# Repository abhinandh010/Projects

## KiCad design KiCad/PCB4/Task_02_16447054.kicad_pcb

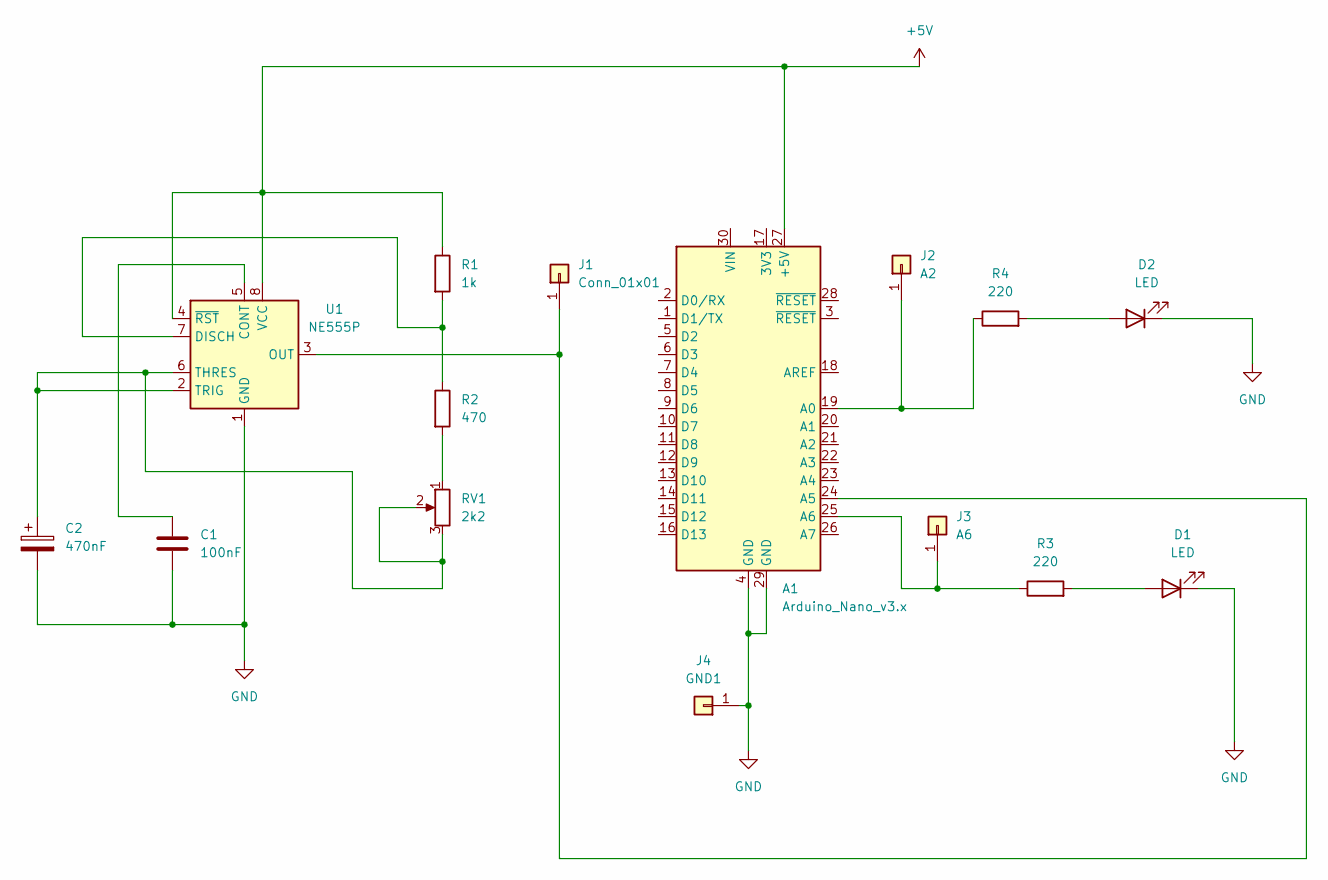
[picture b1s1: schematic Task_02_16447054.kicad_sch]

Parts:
A1: Arduino_Nano_v3.x; Arduino_Nano
C1: 100nF; C_1206_3216Metric_Pad1.33x1.80mm_HandSolder
C2: 470nF; CP_Radial_D5.0mm_P2.00mm
D1, D2: LED; LED_D5.0mm
J1: Conn_01x01; Pin_D1.0mm_L10.0mm
J2: A2; Pin_D1.0mm_L10.0mm
J3: A6; Pin_D1.0mm_L10.0mm
J4: GND1; Pin_D1.0mm_L10.0mm
R1: 1k; R_1206_3216Metric_Pad1.30x1.75mm_HandSolder
R2: 470; R_1206_3216Metric_Pad1.30x1.75mm_HandSolder
R3, R4: 220; R_1206_3216Metric_Pad1.30x1.75mm_HandSolder
RV1: 2k2; Potentiometer_Bourns_3314G_Vertical
U1: NE555P; DIP-8_W7.62mm

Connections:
+5V: A1.27 (+5V), R1.1, U1.4 (~RST), U1.8 (VCC)
GND: A1.4 (GND), A1.29 (GND), C1.2, C2.2, D1.1 (K), D2.1 (K), J4.1 (Pin_1_1), U1.1 (GND)
unnamed: A1.19 (A0), J2.1 (Pin_1_1), R4.1
unnamed: A1.24 (A5), J1.1 (Pin_1_1), U1.3 (OUT)
unnamed: A1.25 (A6), J3.1 (Pin_1_1), R3.1
unnamed: D1.2 (A), R3.2
unnamed: D2.2 (A), R4.2
unnamed: R2.2, RV1.1
unnamed: C1.1, U1.5 (CONT)
unnamed: R1.2, R2.1, U1.7 (DISCH)
unnamed: C2.1, RV1.2, RV1.3, U1.2 (TRIG), U1.6 (THRES)

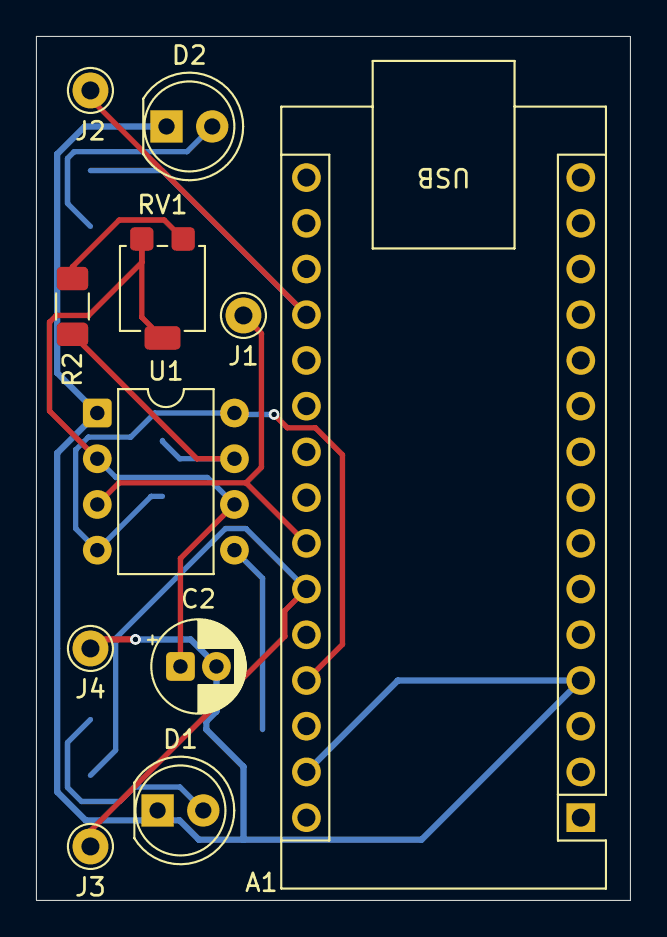
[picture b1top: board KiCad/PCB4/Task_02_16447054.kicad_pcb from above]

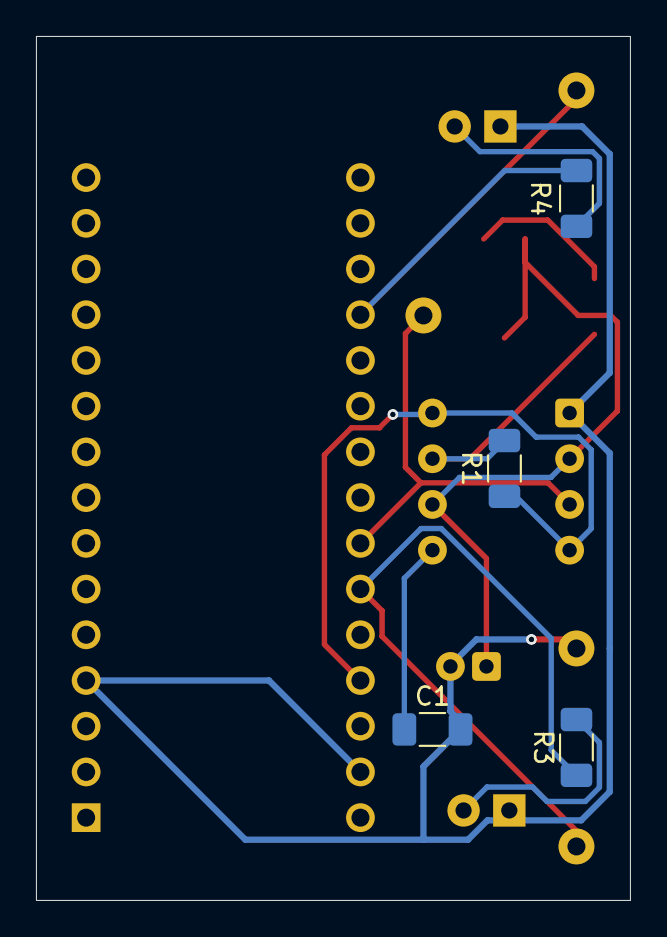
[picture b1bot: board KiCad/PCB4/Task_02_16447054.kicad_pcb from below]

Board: 2 copper layers, 33.0 x 48.0 mm, 15 parts (4 on the bottom side), 11 nets.

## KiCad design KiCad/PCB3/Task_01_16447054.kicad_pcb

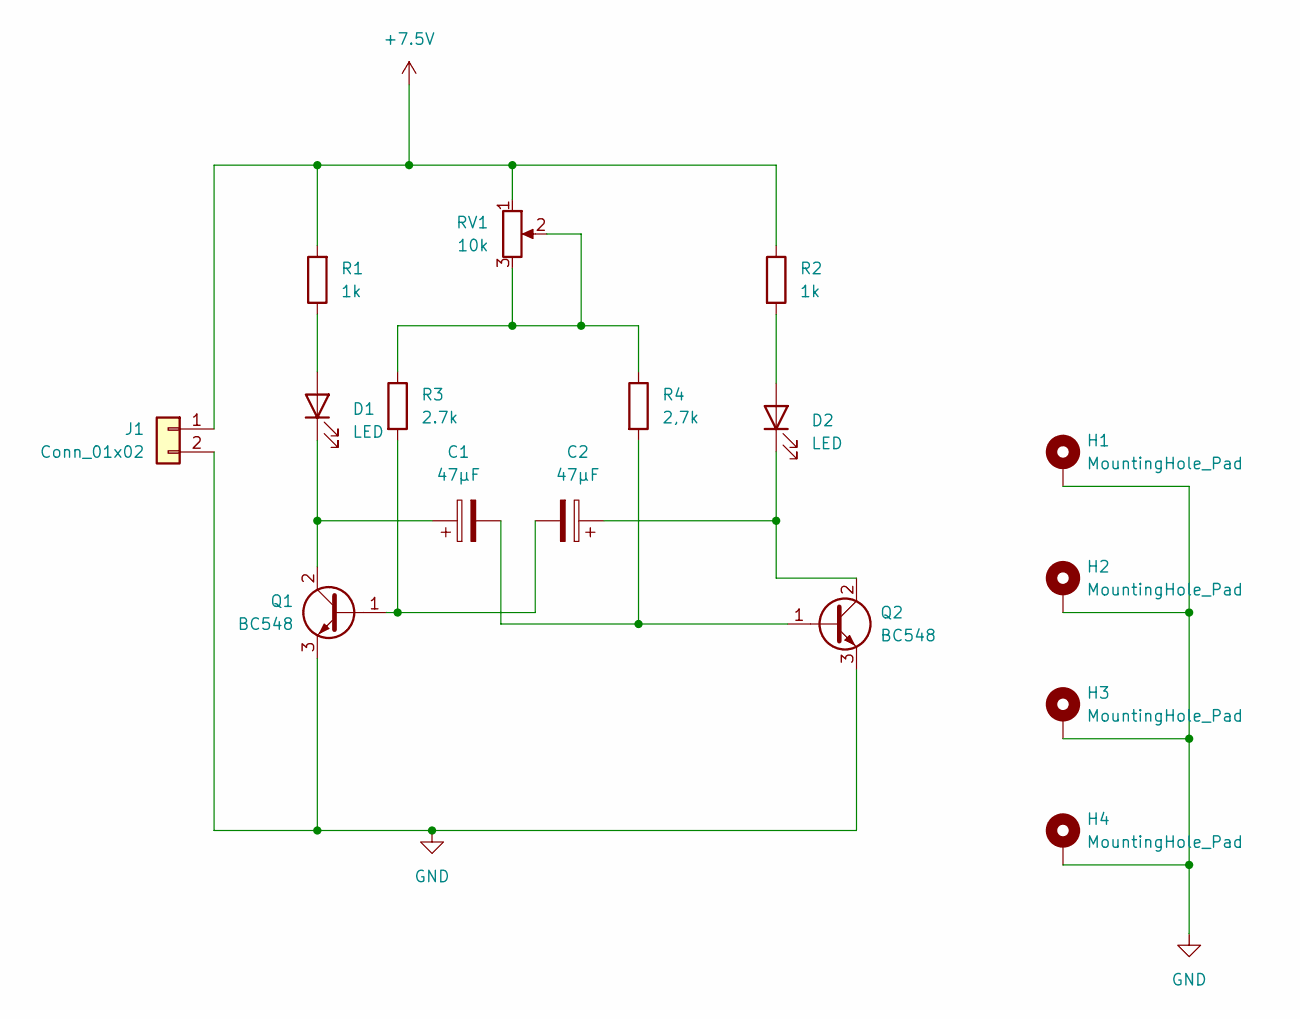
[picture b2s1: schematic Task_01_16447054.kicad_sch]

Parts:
C1, C2: 47µF; CP_Radial_D5.0mm_P2.50mm
D1, D2: LED; LED_D5.0mm
H1, H2, H3, H4: MountingHole_Pad; MountingHole_2.2mm_M2_DIN965_Pad
J1: Conn_01x02; JST_EH_S2B-EH_1x02_P2.50mm_Horizontal
Q1, Q2: BC548; TO-92L_Inline
R1, R2: 1k; R_1210_3225Metric_Pad1.30x2.65mm_HandSolder
R3: 2.7k; R_Axial_DIN0309_L9.0mm_D3.2mm_P15.24mm_Horizontal
R4: 2,7k; R_Axial_DIN0309_L9.0mm_D3.2mm_P15.24mm_Horizontal
RV1: 10k; Potentiometer_Bourns_3266P_Horizontal

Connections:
+7.5V: J1.1, R1.2, R2.1, RV1.1
GND: H1.1 (1_1), H2.1 (1_1), H3.1 (1_1), H4.1 (1_1), J1.2, Q1.3 (E), Q2.3 (E)
unnamed: D1.2 (A), R1.1
unnamed: C1.1, D1.1 (K), Q1.2 (C)
unnamed: D2.2 (A), R2.2
unnamed: C2.1, D2.1 (K), Q2.2 (C)
unnamed: C2.2, Q1.1 (B), R3.2
unnamed: C1.2, Q2.1 (B), R4.2
unnamed: R3.1, R4.1, RV1.2, RV1.3

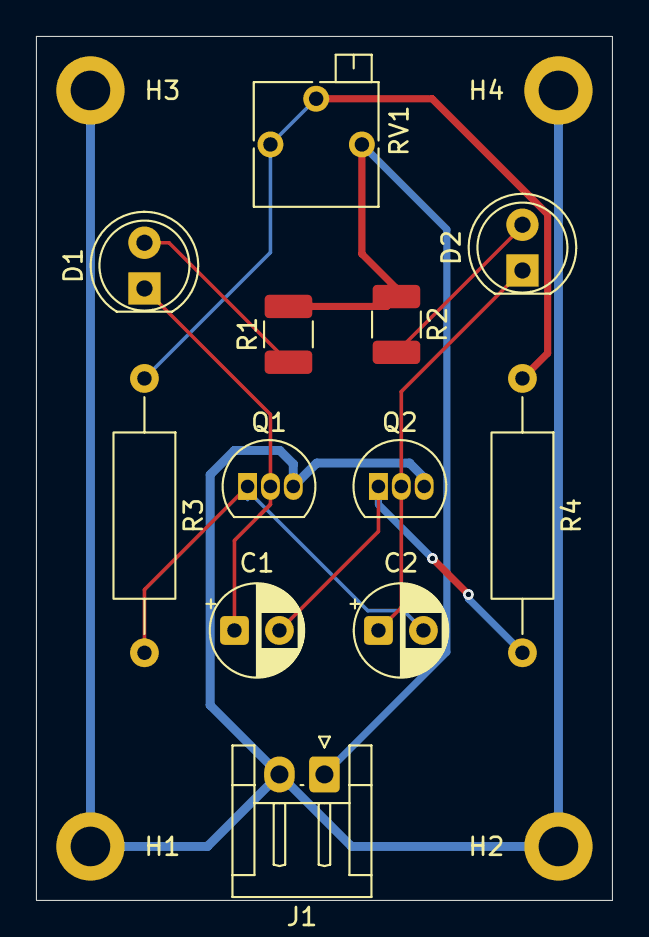
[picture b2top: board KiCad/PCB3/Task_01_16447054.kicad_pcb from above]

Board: 2 copper layers, 32.0 x 48.0 mm, 16 parts (0 on the bottom side), 9 nets.

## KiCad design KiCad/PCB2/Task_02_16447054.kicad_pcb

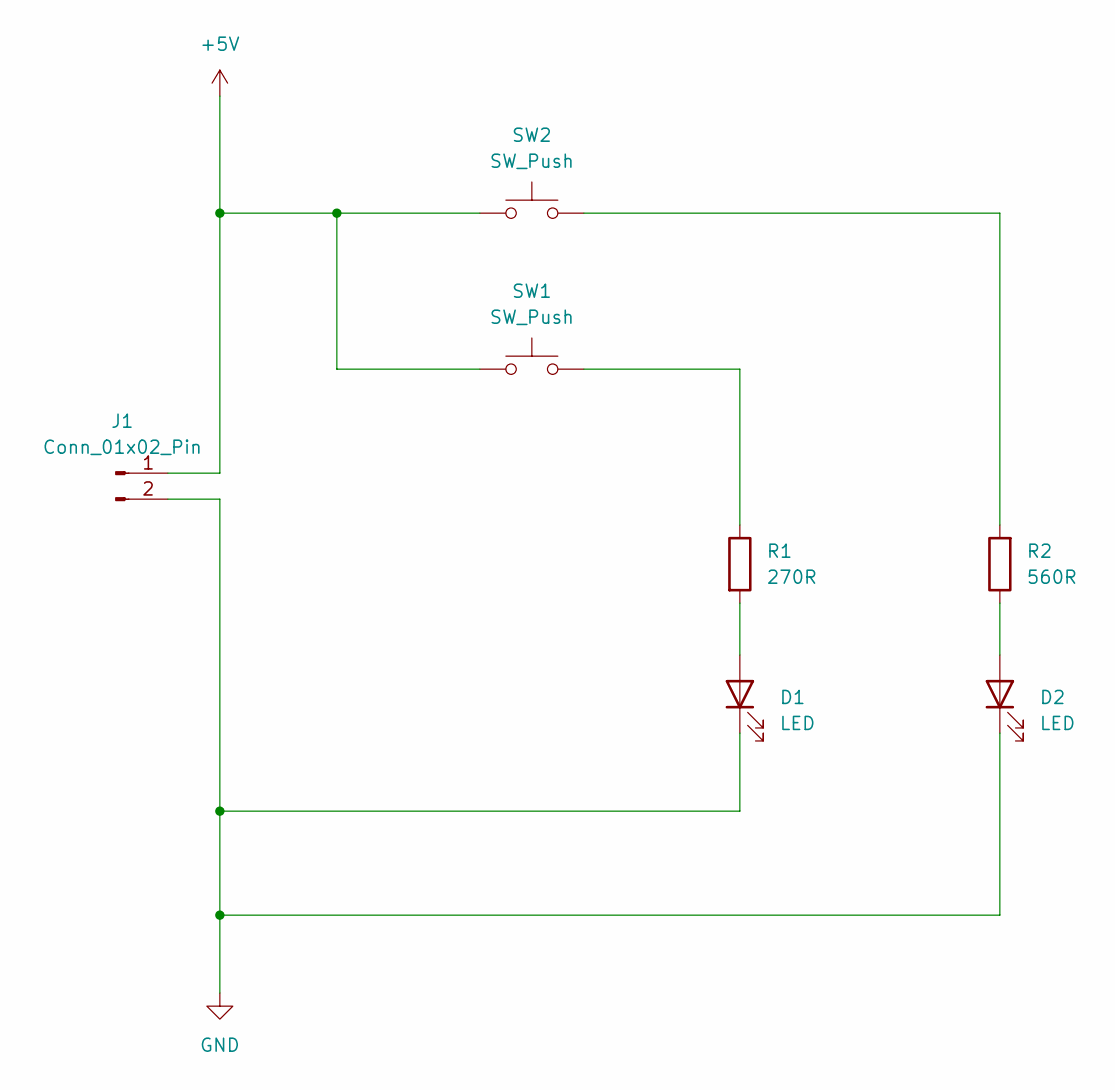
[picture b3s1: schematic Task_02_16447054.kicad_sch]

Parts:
D1: LED; LED_D5.0mm
D2: LED; LED_1206_3216Metric_Pad1.42x1.75mm_HandSolder
J1: Conn_01x02_Pin; JST_EH_B2B-EH-A_1x02_P2.50mm_Vertical
R1: 270R; R_Axial_DIN0309_L9.0mm_D3.2mm_P12.70mm_Horizontal
R2: 560R; R_1206_3216Metric_Pad1.30x1.75mm_HandSolder
SW1, SW2: SW_Push; SW_PUSH_6mm_H7.3mm

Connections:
+5V: J1.1, SW1.1, SW2.1
GND: D1.1 (K), D2.1 (K), J1.2
unnamed: D1.2 (A), R1.2
unnamed: D2.2 (A), R2.1
unnamed: R1.1, SW1.2
unnamed: R2.2, SW2.2

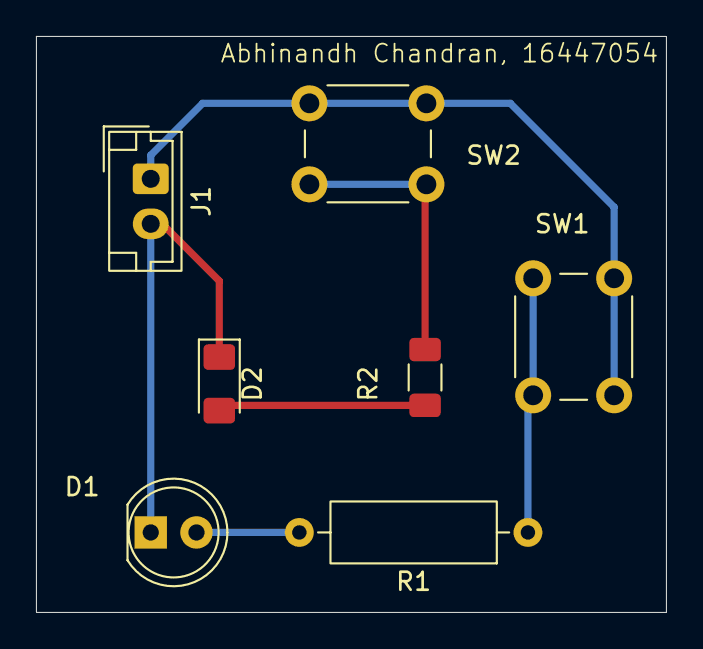
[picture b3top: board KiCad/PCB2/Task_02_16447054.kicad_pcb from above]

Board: 2 copper layers, 35.0 x 32.0 mm, 7 parts (0 on the bottom side), 6 nets.

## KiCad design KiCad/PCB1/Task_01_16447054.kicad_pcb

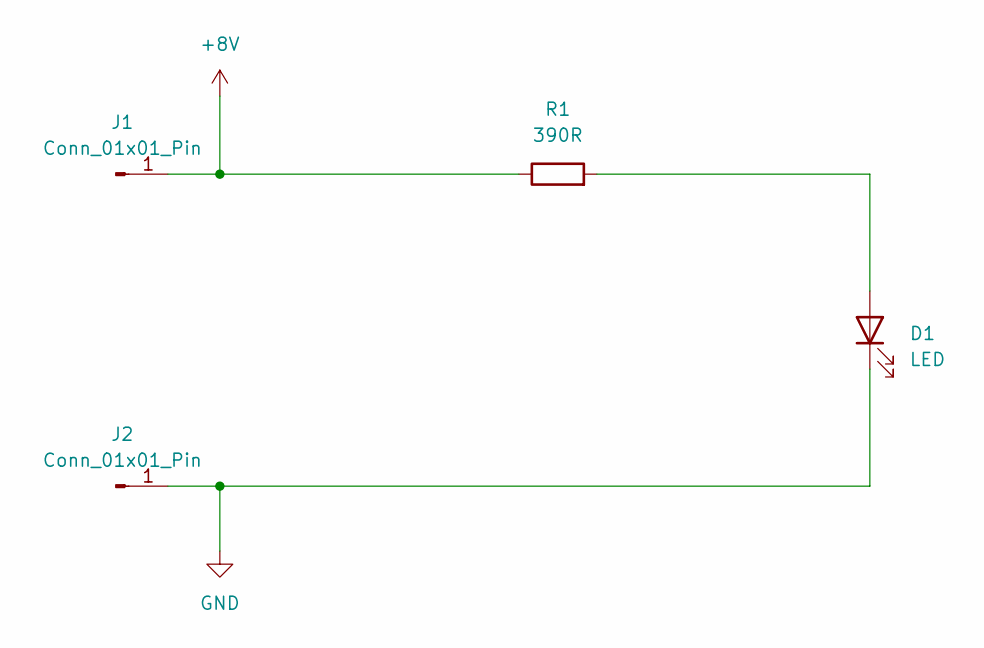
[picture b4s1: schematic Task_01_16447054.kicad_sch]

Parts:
D1: LED; LED_D8.0mm
J1, J2: Conn_01x01_Pin; TestPoint_Loop_D2.54mm_Drill1.5mm_Beaded
R1: 390R; R_Axial_DIN0411_L9.9mm_D3.6mm_P15.24mm_Horizontal

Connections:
+8V: J1.1, R1.1
GND: D1.1 (K), J2.1
unnamed: D1.2 (A), R1.2

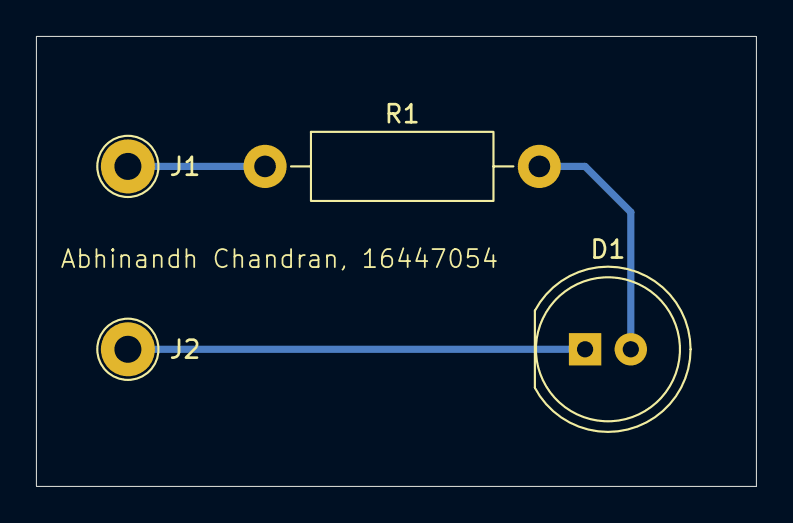
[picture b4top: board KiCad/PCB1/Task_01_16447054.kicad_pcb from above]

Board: 2 copper layers, 40.0 x 25.0 mm, 4 parts (0 on the bottom side), 3 nets.
